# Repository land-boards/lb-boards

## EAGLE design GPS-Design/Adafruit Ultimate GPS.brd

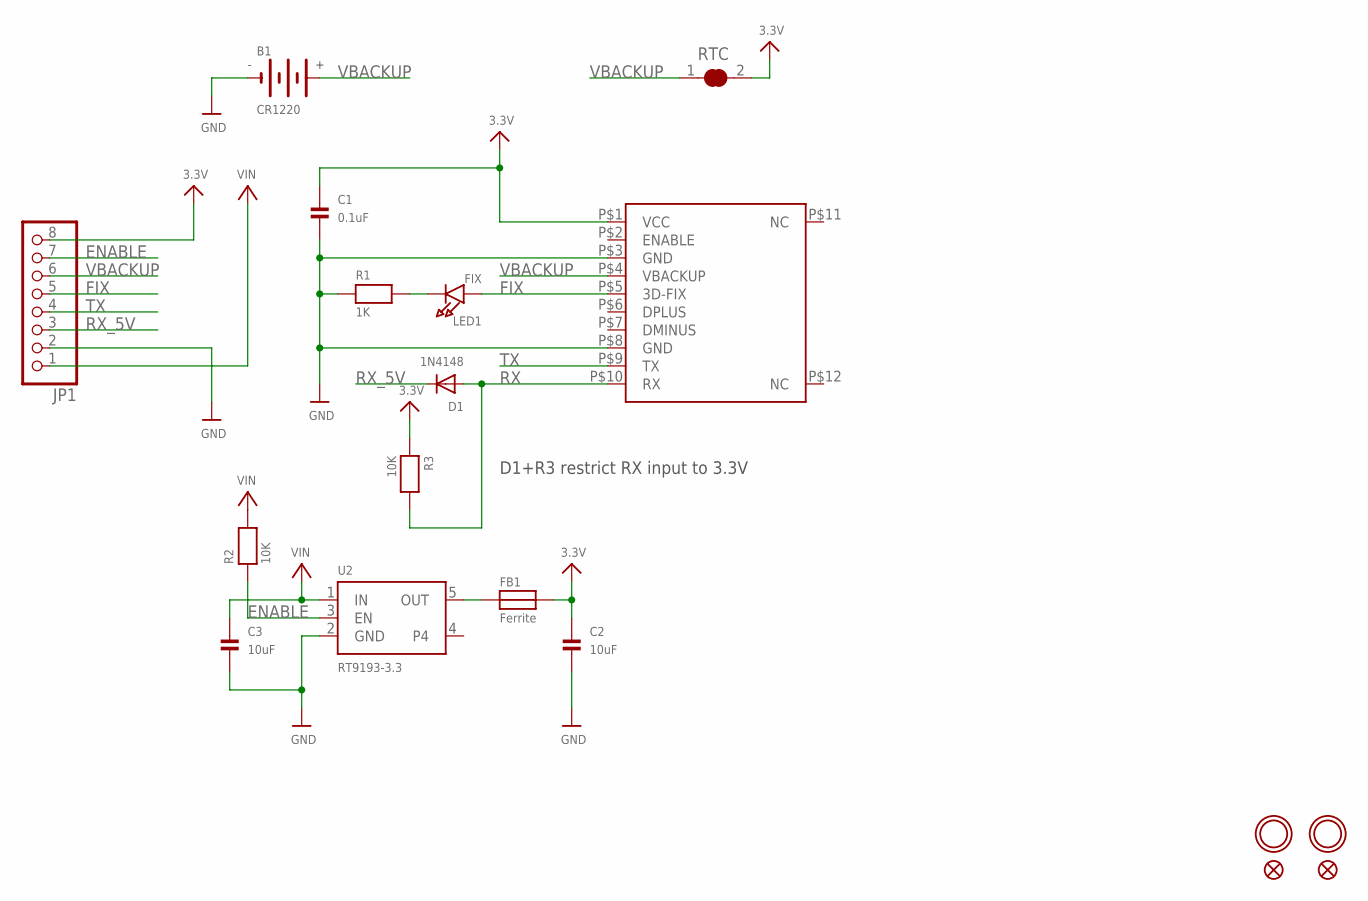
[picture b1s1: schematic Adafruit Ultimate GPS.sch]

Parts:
B1: CR1220
C1: 0.1uF; 0805
C2, C3: 10uF; 0805
D1: 1N4148; SOD-323F
FB1: Ferrite; 0805
FID1, FID2: FIDUCIAL""; FIDUCIAL_1MM
JP1: HEADER-1X870MIL; 1X08_ROUND_70
LED1: FIX; CHIPLED_0805
R1: 1K; 0805
R2, R3: 10K; 0805
RTC: SOLDERJUMPER_CLOSED; SOLDERJUMPER_CLOSEDWIRE
U1: FGPMMOPA6B
U2: RT9193-3.3; SOT23-5
U$8, U$9: MOUNTINGHOLE2.0; MOUNTINGHOLE_2.0_PLATED

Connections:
3.3V: C1.1, C2.1, FB1.2, JP1.8, R3.1, RTC.2, U1.P$1 (VCC)
ENABLE: JP1.7, R2.1, U2.3 (EN)
FIX: JP1.5, LED1.A, U1.P$5 (3D-FIX)
GND: B1.-, C1.2, C2.2, C3.2, JP1.2, R1.1, U1.P$3 (GND), U1.P$8 (GND), U2.2 (GND)
unnamed: LED1.C, R1.2
unnamed: FB1.1, U2.5 (OUT)
RX: D1.A, R3.2, U1.P$10 (RX)
RX_5V: D1.C, JP1.3
TX: JP1.4, U1.P$9 (TX)
VBACKUP: B1.+$1 (+), JP1.6, RTC.1, U1.P$4 (VBACKUP)
VIN: C3.1, JP1.1, R2.2, U2.1 (IN)

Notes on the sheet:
D1+R3 restrict RX input to 3.3V

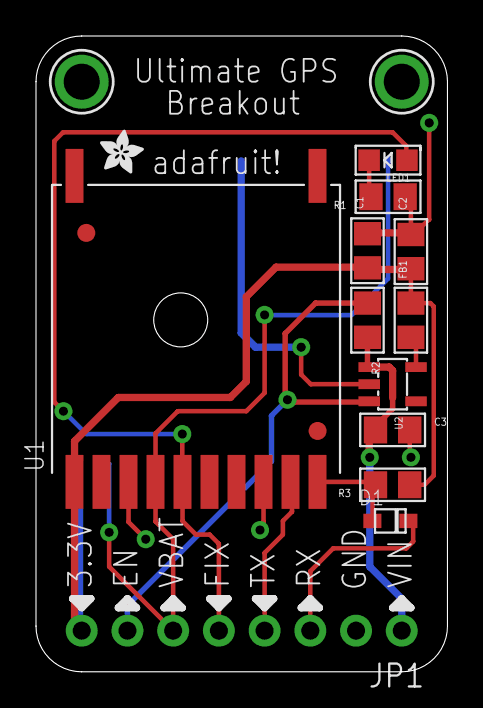
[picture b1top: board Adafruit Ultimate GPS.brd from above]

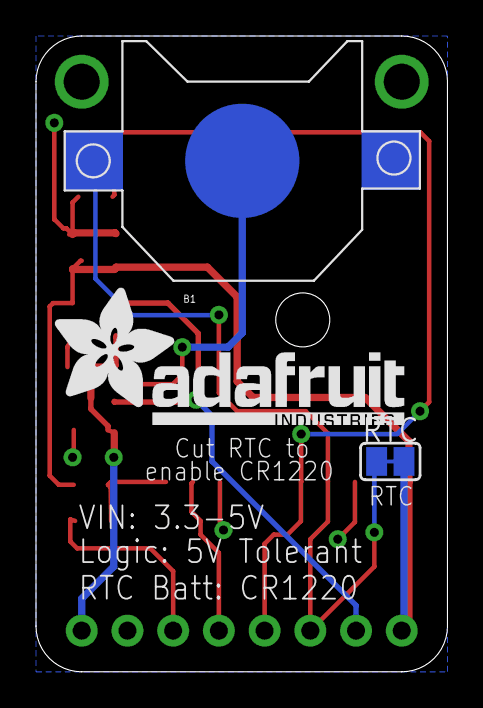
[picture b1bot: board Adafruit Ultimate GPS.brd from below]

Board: 2 copper layers, 22.9 x 35.3 mm, 20 parts (3 on the bottom side), 11 nets.

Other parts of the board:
U$15: ADAFRUIT_2.5MM
U$16: ADAFRUIT_TEXT_20MM
